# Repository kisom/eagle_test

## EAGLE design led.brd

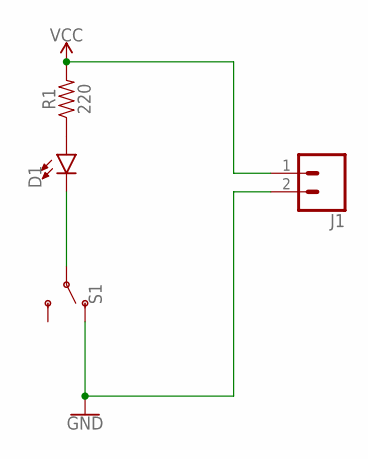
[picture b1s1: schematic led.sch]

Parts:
D1: LED5MM; LED_5MM
J1: CONN_02LOCK; 1X02_LOCK
R1: 220; AXIAL-0.3
S1: SWITCH-SPDT-PTH-11.6X4.0MM-LOCK; SWITCH_SPDT_PTH_11.6X4.0MM_LOCK

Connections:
GND: J1.2, S1.1 (O)
unnamed: D1.K (C), S1.2
unnamed: D1.A, R1.P$1 (1)
VCC: J1.1, R1.P$2 (2)

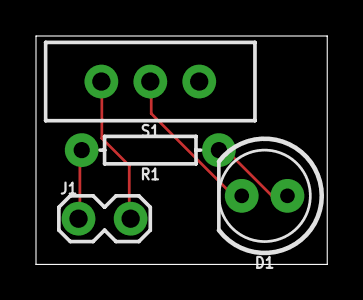
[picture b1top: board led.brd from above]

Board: 2 copper layers, 16.2 x 12.7 mm, 4 parts (0 on the bottom side), 4 nets.

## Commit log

2018-12-28 Initial commit.
2018-12-28 Whoops! Forgot a resistor!

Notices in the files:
parts and their libraries:
SparkFun-LED: Licensing: Creative Commons ShareAlike 4.0 International - https://creativecommons.org/licenses/by-sa/4.0
